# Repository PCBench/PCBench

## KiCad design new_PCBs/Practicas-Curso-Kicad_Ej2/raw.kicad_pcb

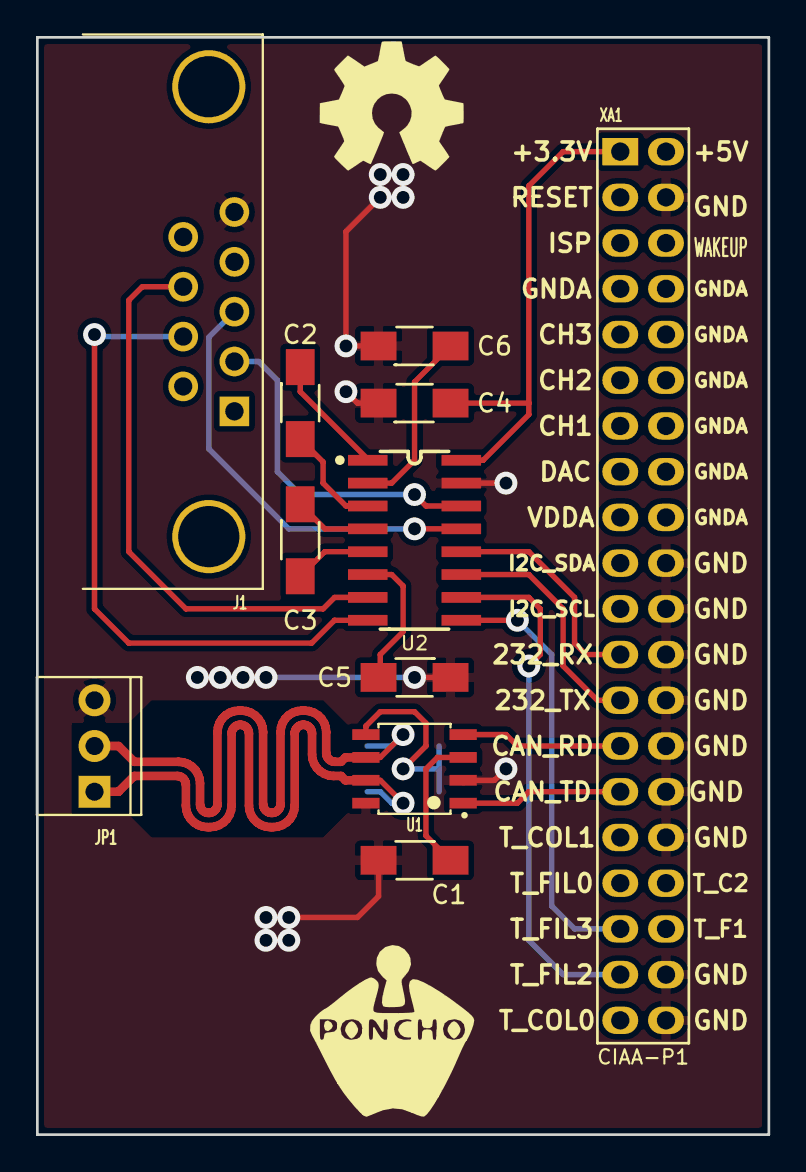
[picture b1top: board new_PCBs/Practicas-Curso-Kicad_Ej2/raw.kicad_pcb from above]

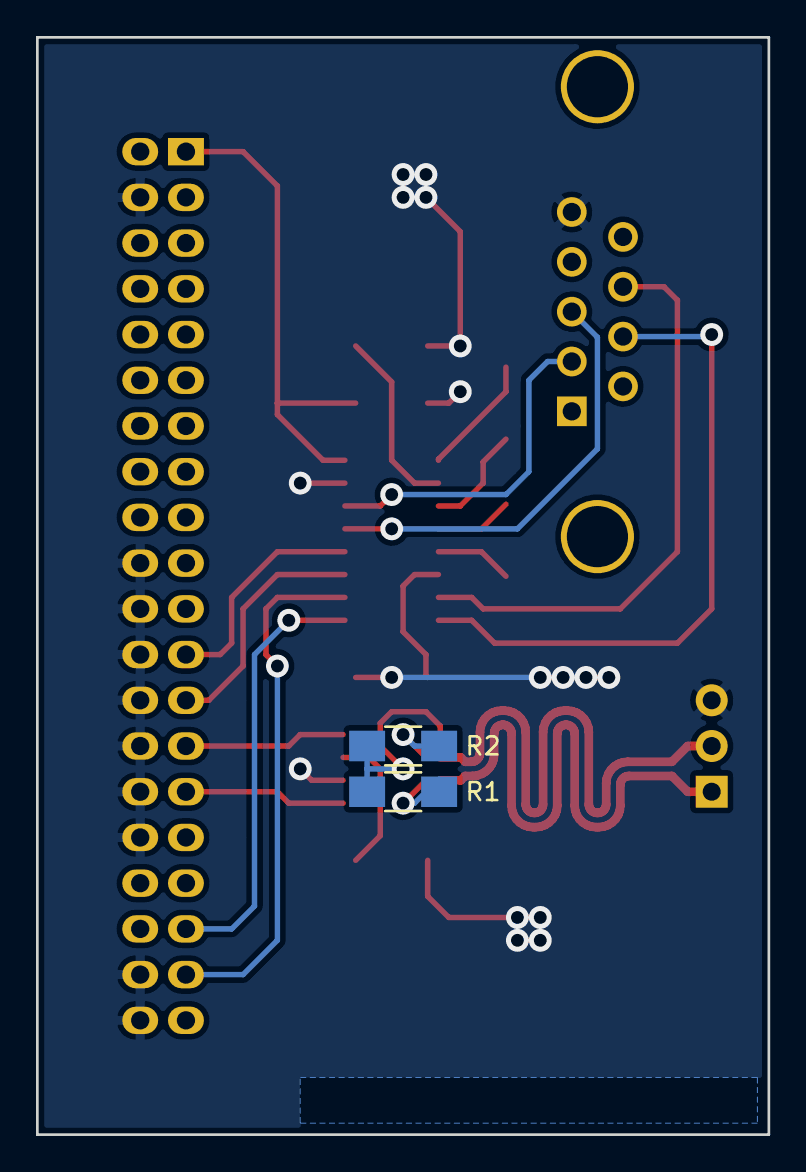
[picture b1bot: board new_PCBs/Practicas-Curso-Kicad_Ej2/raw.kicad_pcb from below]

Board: 2 copper layers, 40.6 x 61.0 mm, 14 parts (2 on the bottom side), 22 nets.

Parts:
C1, C2, C3, C4, C5, C6: 100nF; C_1206_Handsoldering
G101: Logo_OSHWA
J1: DB9; DB9_F_TH
JP1: CONN_3; CON_PALETA_3
R1, R2: 60; R_1206_HandSoldering
U1: AMIS42665TJAA1RG; SOIC-8
U2: SP3232DC; SP3232ECN-SOIC16N
XA1: Conn_Poncho2P_2x_20x2; Conn_Poncho_Derecha

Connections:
+3.3V: C4.1, U2.16, XA1.1
/Conector y CAN/CAN_N: JP1.2, R2.2, U1.6
/Conector y CAN/CAN_P: JP1.1, R1.1, U1.7
/Conector y CAN/CAN_RX: U1.4, XA1.27
/Conector y CAN/CAN_TX: U1.1, XA1.29
/Conector y CAN/CTS: U2.10, XA1.37
/Conector y CAN/RTS: U2.9, XA1.35
/Conector y CAN/RXD: U2.11, XA1.25
/Conector y CAN/TXD: U2.12, XA1.23
GND: C1.1, C4.2, C5.2, C6.2, J1.5, JP1.3, U1.2, U1.8, U2.15, XA1.4, XA1.20, XA1.22, XA1.24, XA1.26, XA1.28, XA1.30, XA1.32, XA1.38, XA1.40
unnamed: C1.2, U1.3
unnamed: C2.1, U2.3
unnamed: C2.2, U2.1
unnamed: C3.1, U2.5
unnamed: C3.2, U2.4
unnamed: C5.1, U2.6
unnamed: C6.1, U2.2
unnamed: J1.2, U2.14
unnamed: J1.3, U2.13
unnamed: J1.7, U2.8
unnamed: J1.8, U2.7
unnamed: R1.2, R2.1, U1.5

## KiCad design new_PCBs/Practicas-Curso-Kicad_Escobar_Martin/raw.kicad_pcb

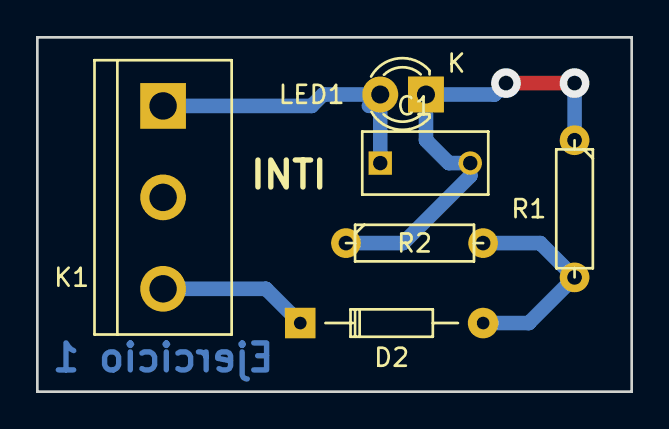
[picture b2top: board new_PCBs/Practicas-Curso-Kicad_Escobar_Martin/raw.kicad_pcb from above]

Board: 2 copper layers, 33.0 x 19.7 mm, 6 parts (0 on the bottom side), 4 nets.

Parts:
C1: 100nF; C_Rect_L7_W3.5_P5
D2: 1N4148; Diode_DO-35_SOD27_Horizontal_RM10
K1: CONN_3; bornier3
LED1: LED_ROJO; LED-3MM
R1, R2: 100K; R3-LARGE_PADS

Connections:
unnamed: C1.1, K1.1, LED1.2
unnamed: C1.2, LED1.1, R1.1, R2.1
unnamed: D2.1, K1.3
unnamed: D2.2, R1.2, R2.2
